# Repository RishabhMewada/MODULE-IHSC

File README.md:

# MODULE-IHSC
A thermal imaging module consisting of XIAO RP2040 &amp; MLX90640 for thermal camera and XIAO for the onboard processing 
which supports usb type c streaming and usb screen sharing extension via an 4 pin I2C extension

-------------------------------------------------------------------------------------------------
## Purpose 
The goal of this project was to design a low profile thermal camera module capable of streaming live
footage over to the screen via type c and I2C pins

things considerd in mind to make it happen
- PCB design
- CAD 
- Components
- Firmware modularization and easy modification

-------------------------------------------------------------------------------------------------
## Features

*Core Hardware*

- XIAO RP2040
- MLX90640  
- 4 Pin I2C horizontal pins 
- buzzer for beeping
- tactile switch
- transistor
 
-------------------------------------------------------------------------------------------------
## Transport & Connectivity

 - 4 Pin I2C horizontal pins 
- USB-C connection
-------------------------------------------------------------------------------------------------
## Hardware
The PCB is designed using KiCad (open-source) and the case using Fusion 360.

Specifications

- 2-layer PCB
- XIAO RP2040 Proccessing
- MLX90640  heat Camera
- I²C  4 pin connector
- 
All PCB source files are available in `/hardware/kicad`.

-------------------------------------------------------------------------------------------------

## Firmware

- Thermal Sensing camera

*Raw MLX90640 32×24 thermal array with 768 pixels, connected directly via I2C
with 110° wide field of view built into the camera
and have the abillity to measure −40 °C to +300 °C measurement range
Dual I2C bus architecture — sensor on I2C1 (GP6/GP7), display on I2C0 (GP4/GP5) to prevent bus conflicts*

- Rainbow Heatmap

*Full 7-stop rainbow colour mapping (violet → blue → cyan → green → yellow → orange → red)
Bicubic interpolation upscaling from 32×24 to full display resolution which will convert it into 
Real-time hotspot and coldspot crosshair overlays with temperature labels
Live temperature scale bar rendered on-screen*

- Dual Output System

*USB-CDC mode — binary frame stream over via a Type-C cable to a PC host viewer
I2C display mode — frames rendered directly onto an external OLED via the 4-pin PCB connector (SSD1306 128×64 or SH1107 128×128)
BOTH mode — simultaneous USB stream and I2C display output
Smart startup auto-detection: defaults to BOTH if display and USB host are both detected, I2C is used only if no PC is connected or USB if no display is found*

- Output Switching

*Short-press mode button cycles USB → I2C → BOTH → USB in real time
Long-press mode button saves current mode to flash (persists across reboots)
PC-side display_switch.py utility to switch modes remotely over USB without touching the device
Soft-reset trigger from PC so new mode activates immediately without unplugging* (made for future integration)

- PC Host Viewer (host_display.py)

*Live OpenCV window with rainbow heatmap whit support up to 30 fps
Bicubic interpolation for smooth upscaled display
Adjustable window scale factor
and it Cycle's through 5 colour maps: Rainbow, Inferno, Plasma, Bone, Jet
and the Temperature range lock/unlock (freeze min–max for consistent colour mapping)
and shows Hotspot and coldspot crosshairs with live °C labels and it has a 
Full-screen toggle
Live FPS counter and frame index overlay*

- PC Switch Utility (display_switch.py)

*Query current output mode from the device which 
Switchs to the output mode (USB / I2C / BOTH) via command line and
Scan the 4-pin I2C connector bus to detect connected display hardware and then
 the Live frame monitor — prints per-frame FPS, Tmin, Tmax, and checksum status and it also
Auto-detects RP2040 serial port (no --port flag needed in most cases)*

- Performance

*~30 fps live thermal stream at 32 Hz sensor refresh rate in the MLX90640 camera
-USB-CDC frame size: 1562 bytes per frame (~47 KB/s, well within USB bandwidth)
 and uses Binary framing protocol with magic header and checksum validation for data integrity
and Frame index tracking for dropped frame detection*

- Hardware Controls

*Power button (GP28): short press pauses/resumes streaming; long press enters light-sleep
Mode button (GP29): short press cycles output mode; long press saves mode to flash
Buzzer (GP27): distinct beep patterns for each event — power-on, mode switch (unique per mode), mode saved, sleep, and error*

- Buzzer Feedback

Single long beep on power-on
1 beep = USB mode selected
2 beeps = I2C display mode selected
3 beeps = BOTH mode / mode saved to flash
Double beep = entering sleep
5 rapid beeps = sensor not found (wiring error)

- Persistent Configuration

*Output mode saved to output_mode.json on the RP2040's onboard flash
Automatically restored on every reboot with no user intervention*

Firmware files are located in `/firmware`.

-------------------------------------------------------------------------------------------------
## Images

-------------------------------------------------------------------------------------------------
## BOM
The complete bill of materials (BOM), including purchase links, is available in  
`/hardware/bom.csv`.

Manufacturing & sourcing:
- PCB fabrication: **JLCPCB**
- Components (India): **Robu.in**
- Enclosure: Online 3D printing services (if needed)

## Bill of Materials

| Name | Quantity | Total Cost (USD) | Distributor | Link |
|------|----------|-----------------|-------------|------|
| PCB | 5 | $8.00 | JLCPCB | [Buy](https://cart.jlcpcb.com/shopcart/cart/) |
| Soldering Flux | 1 | $0.27 | Robu.in | [Buy](https://robu.in/product/noel-flux-soldering-paste-10g) |
| MLX90640 | 1 | $37.48 | Digikey.in | [Buy](https://www.digikey.in/en/products/detail/melexis-technologies-nv/MLX90640ESF-BAA-000-SP/8638465) |
| XIAO RP2040 | 1 | $6.41 | Robocraze.in | [Buy](https://robocraze.com/products/seeed-studio-xiao-rp2040-development-board?variant=47742255562976&country=IN&currency=INR&campaignid=23145906364&adgroupid=182236965810&keyword=&device=c&gad_campaignid=23145906364) |
| Buzzer (BZ1) | 1 | $0.15 | Robu.in | [Buy](https://robu.in/product/3v-active-electromagnetic-buzzer-pack-of-5) |
| 1×4 Pin Header (J1) | 1 | $0.14 | Robu.in | [Buy](https://robu.in/product/ds1022-22-1x10ruf1-a3-0-b6-0-c6-0-b-connfly-1x10-pin-2-54mm-pin-header-r-a-type-h2-0mm) |
| Low Profile Tactile Switch SMD | 1 | $0.11 | Robu.in | [Buy](https://robu.in/product/tsc008a1718a-bzcn-4x4x1-7mm-50ma-round-button-50gf-12v-smd-tactile-switches-rohs) |
| Resistor 4.7 kΩ 0603 (R2) | 2 | $0.11 | Robu.in | [Buy](https://robu.in/product/4-7k-ohm-1-4w-0603-surface-mount-chip-resistor-pack-of-100) |
| Resistor 1 kΩ 0805 (R1) | 1 | $0.11 | Robu.in | [Buy](https://robu.in/product/1k-ohm-1-4w-0805-surface-mount-chip-resistor-pack-of-10) |
| Capacitor 100 nF 0805 (C1) | 1 | $0.12 | Robu.in | [Buy](https://robu.in/product/cs2012x7r106m100nre-samwha-10v-10uf-x7r-%c2%b120-0805-multilayer-ceramic-capacitors-mlcc-smd-smt-rohs) |
| Capacitor 1 µF 0603 (C3) | 1 | $0.11 | Robu.in | [Buy](https://robu.in/product/1uf-1000nf-50v-capacitor-0603-smd-package-pack-of-20) |
| Capacitor 10 µF 0805 (C2) | 1 | $0.11 | Robu.in | [Buy](https://robu.in/product/100nf-0805-surface-mount-multilayer-ceramic-capacitor-pack-of-40) |
| 2N2219 Transistor | 1 | $ | link |
| **Total** | | **$77.81** | | |

please note that most of the parts are from indian suppliers !

*note there's also a transistor in the project (2N2219) but it's not available anywhere online for me that's why it's not included in the BOM with price and link

-------------------------------------------------------------------------------------------------
## License
This project is open-source hardware and software and is released under the **MIT License**.

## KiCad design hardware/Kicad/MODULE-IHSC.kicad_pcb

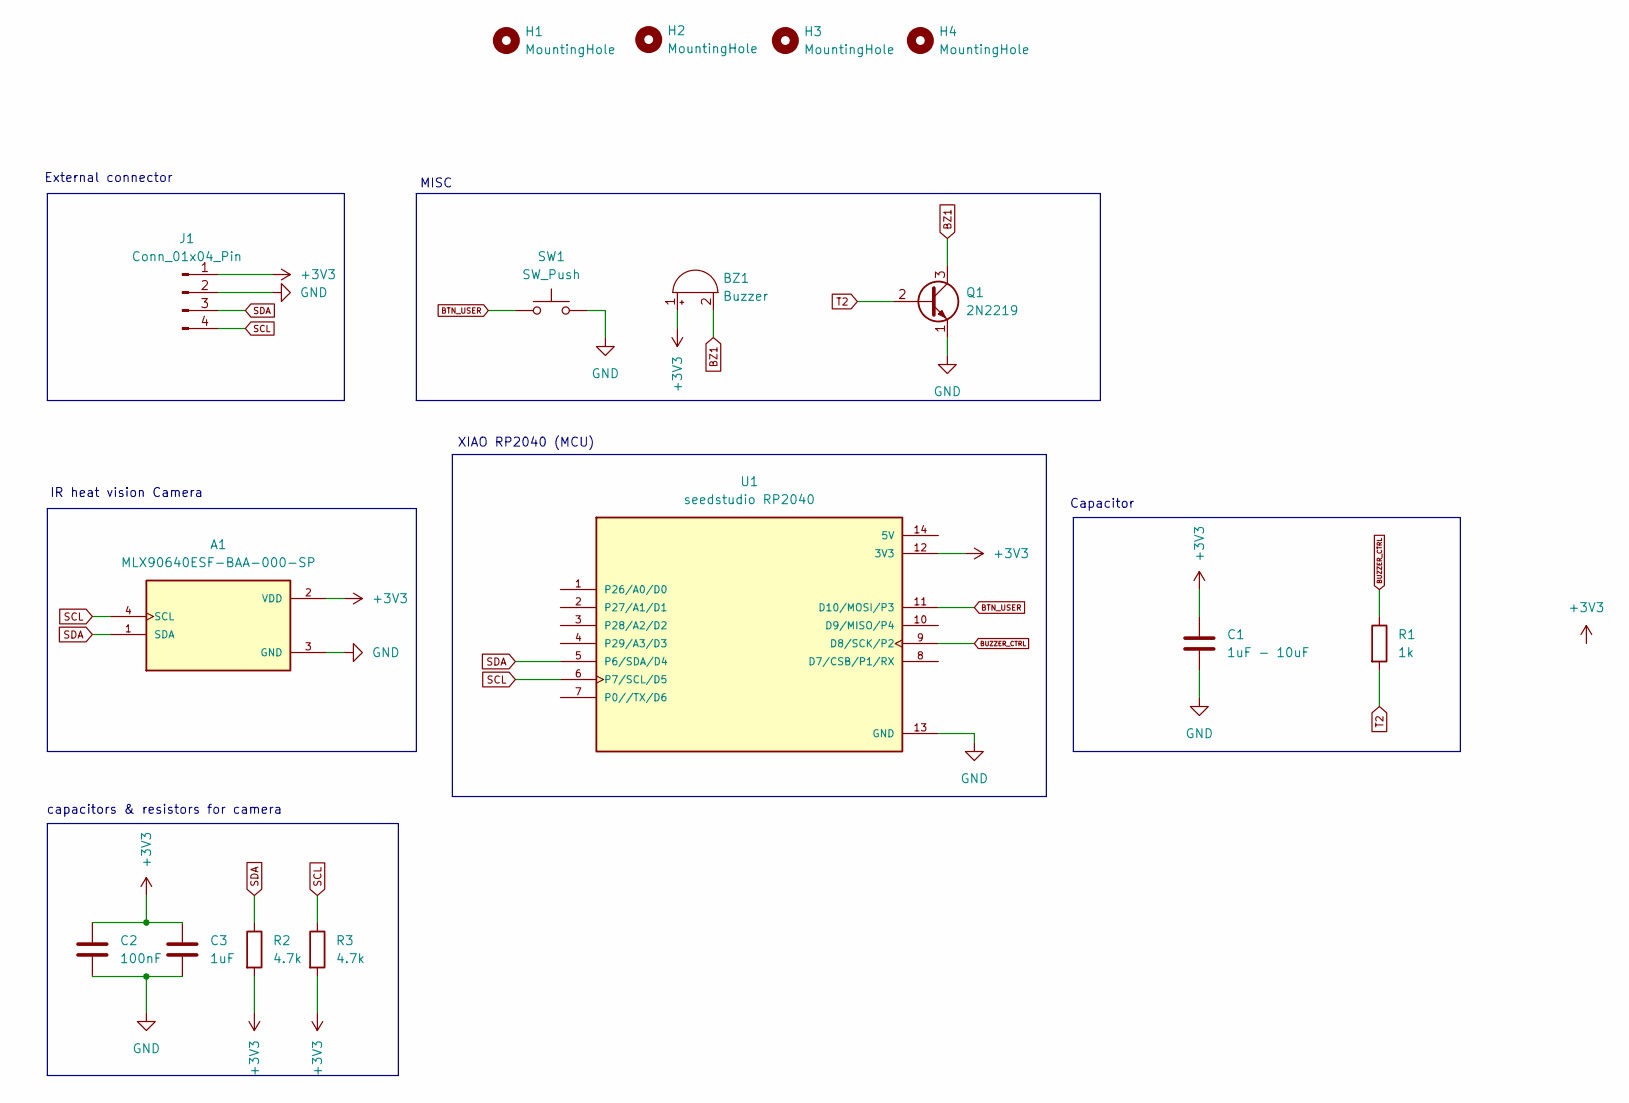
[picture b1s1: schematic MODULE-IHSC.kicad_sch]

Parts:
A1: MLX90640ESF-BAA-000-SP; TO292P930H600-4
BZ1: Buzzer; Buzzer_12x9.5RM7.6
C1: 1uF - 10uF; C_0805_2012Metric
C2: 100nF; C_0603_1608Metric
C3: 1uF; C_0603_1608Metric
H1, H2, H3, H4: MountingHole; MountingHole_2.1mm
J1: Conn_01x04_Pin; PinHeader_1x04_P2.54mm_Horizontal
Q1: 2N2219; TO-39-3
R1: 1k; R_0805_2012Metric
R2, R3: 4.7k; R_0603_1608Metric
SW1: SW_Push; SW_SPST_TL3342
U1: seedstudio RP2040; MODULE_102010428; DigiKey_Part_Number 1597-102010428-ND

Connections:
SCL: A1.4 (SCL), J1.4, R3.1, U1.6 (P7/SCL/D5)
+3V3: A1.2 (VDD), BZ1.1 (+), C1.1, C2.1, C3.1, J1.1, R2.2, R3.2, U1.12 (3V3)
BTN_USER: SW1.1, U1.11 (D10/MOSI/P3)
BUZZER_CTRL: R1.1, U1.9 (D8/SCK/P2)
BZ1: BZ1.2 (-), Q1.3 (C)
GND: A1.3 (GND), C1.2, C2.2, C3.2, J1.2, Q1.1 (E), SW1.2, U1.13 (GND)
SDA: A1.1 (SDA), J1.3, R2.1, U1.5 (P6/SDA/D4)
T2: Q1.2 (B), R1.2

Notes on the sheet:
MISC
XIAO RP2040 (MCU)
IR heat vision Camera
Capacitor
capacitors & resistors for camera
External connector

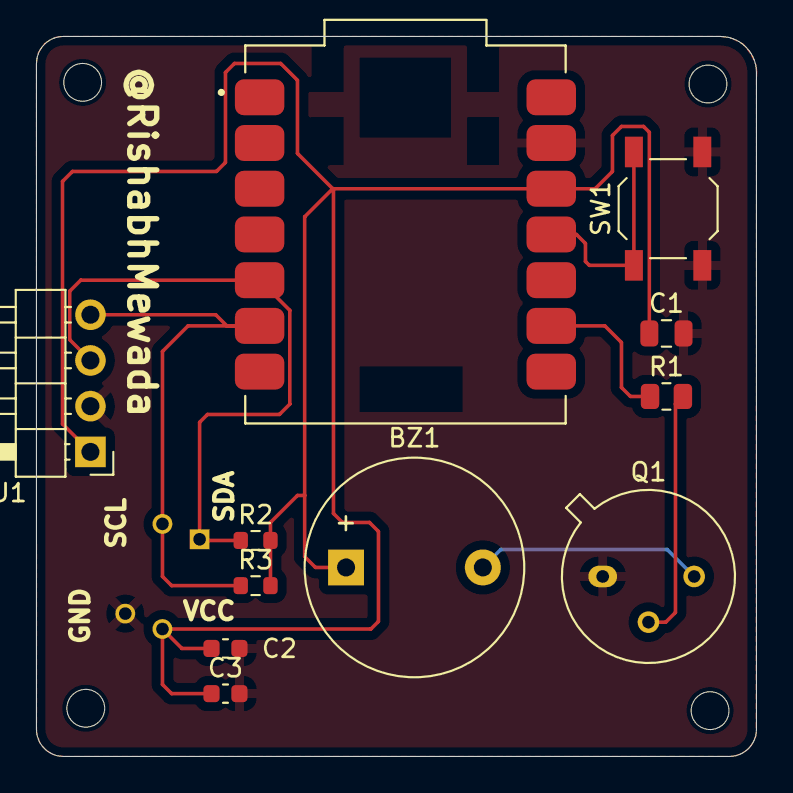
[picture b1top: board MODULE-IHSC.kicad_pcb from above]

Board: 2 copper layers, 40.0 x 40.0 mm, 16 parts (1 on the bottom side), 8 nets.

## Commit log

2026-05-14 Rename MODULE-IHSC-bom (1).csv to MODULE-IHSC-bom .csv
